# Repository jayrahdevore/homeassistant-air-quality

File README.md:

# Air Quality Sensor for Home Assistant

- [x] Component Testing
  - [x] Get sensor data from SPS30 using example code
  - [x] Get sensor data from ENS160 using example code
  - [x] Publish data to Home Assistant via MQTT
    - [x] Basic device discovery
    - [x] Device discovery w/ description and fields
    - [x] Publish fake data to Home Assistant
- [x] Proof of Concept
  - [x] Combine data from both sensors and send over serial
  - [x] Read data from serial and publish over MQTT
- [ ] Productize using Pico W
  - [ ] Send device discovery and fake data over MQTT
  - [ ] Wire up sensors to Pico W
  - [ ] Retrieve data from SPS30
  - [ ] Retrieve data from ENS160
  - [ ] Design and build enclosure

## LICENSE

Orignal work in this repository is licensed into the public domain. Works taken
from other projects (i.e. example code .ino files) retain their original
licenses and are marked in their header as such.

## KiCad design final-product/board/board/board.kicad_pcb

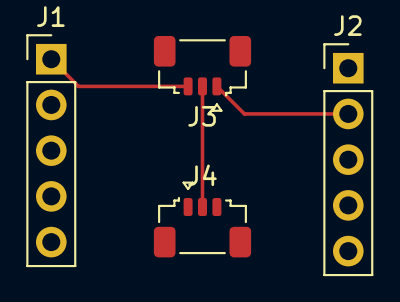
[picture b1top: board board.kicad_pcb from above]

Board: 2 copper layers, 4 parts (0 on the bottom side), 5 nets.

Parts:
J1, J2: Conn_01x05_Pin; PinHeader_1x05_P2.54mm_Vertical
J3, J4: Conn_01x04_Socket; JST_SUR_SM03B-SURS-TF_1x03-1MP_P0.80mm_Horizontal

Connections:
+3.3V: J1.5, J4.3
+5V: J1.1, J3.3
GND: J1.3, J2.3
unnamed: J2.1, J3.2, J4.2
unnamed: J2.2, J3.1, J4.1

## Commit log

2024-09-14 Add working example of device discovery and publish
2024-09-14 Finished POC - now it's publishing to Home Assistant
2024-09-18 WIP: micropython final product
2024-09-19 Add beginnings of the PCB
